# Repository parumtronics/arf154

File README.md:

# arf154 

Arf154 is an arduino compatible wireless network ready board.

The board core is the atsamr21g1x SoC. The device integrates a Cortex-M0 and a
IEEE 802.15.4 transceiver.

## Footprint

The design is targeting to be as compatible as possible with Arduino nano.

## How to program

The board can be programmed using the USB connector or trough the EMDBG using 
any Atmel software tools.

## Libraries

At this moment, there's no library but basic wireless communication libraries 
will be added in near future. Support for advanced features, as mesh network,
will be added later.

The board also is compatible with zigbee, 6lowpan and other network standart.

## Status

At this moment the schematics are almost done.

LICENSE: All work is released under the MIT license.

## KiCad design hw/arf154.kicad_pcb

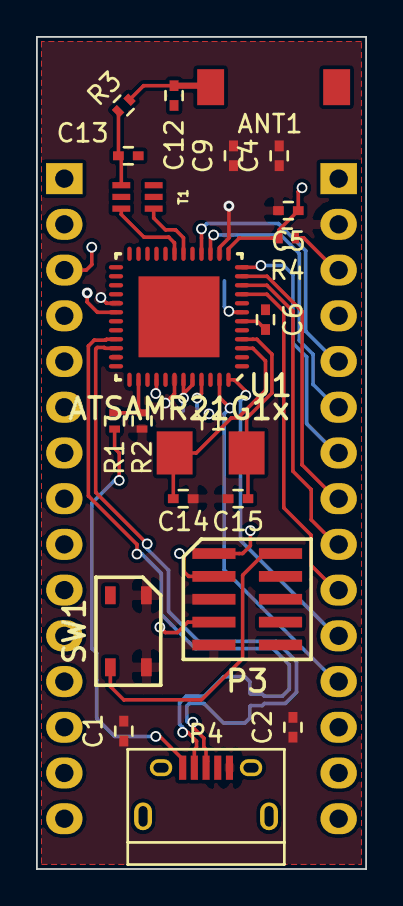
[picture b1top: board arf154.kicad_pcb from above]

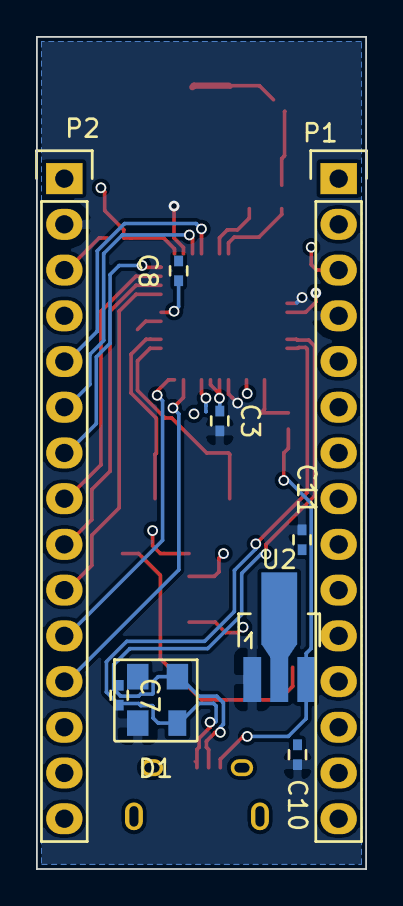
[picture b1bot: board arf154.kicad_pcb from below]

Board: 4 copper layers, 18.3 x 46.2 mm, 30 parts (9 on the bottom side), 27 nets.

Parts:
ANT1: antenna; CHIPANTENNA2dBi
C1: 10uF; C_0402
C2, C3, C4, C5, C6, C7, C8, C10: 100n; C_0402
C9, C11: 10u; C_0402
C12, C13: xF; C_0402
C14, C15: 18pF; C_0402
D1: PRTR5V0U2X; SOT143B
P1: Cn1; Pin_Header_Straight_1x15
P2: Cn2; Pin_Header_Straight_1x15
P3: CONN_02X05; CMxDBG
P4: USB_B; USB_Micro-B
R1, R2: 100K; R_0402
R3: xR; R_0402
R4: 10K; R_0402
SW1: SW_PUSH; tactileswitch
T1: 2450BM15A0015; JBALUN
U1: ATSAMR21G1x; QFN48EP
U2: AZ1117C; SOT89-3_Housing_Handsoldering
Y1: 16MHz; 2SMD

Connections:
/MainProcessor/BD+: T1.4, U1.18
/MainProcessor/BD-: T1.3, U1.19
/MainProcessor/PA4: P2.10, U1.9
/MainProcessor/PA5: P2.9, U1.10
/MainProcessor/PA6: P2.8, U1.11
/MainProcessor/PA7: P2.7, U1.12
/MainProcessor/PA8: P2.6, U1.15
/MainProcessor/PA9: P2.5, U1.16
/MainProcessor/PA22: U1.31, U1.37
/MainProcessor/PA23: R1.2, R2.1, U1.32, U1.38
/MainProcessor/PB2: P2.12, U1.47
/MainProcessor/PB3: P2.11, U1.48
/MainProcessor/RST: C7.1, P1.3, P2.3, P3.10, R4.1, SW1.2, U1.40
/MainProcessor/SWCLK: P3.4, U1.45
/MainProcessor/SWDIO: P3.2, U1.46
/Sheet557215E3/D+: D1.3, P4.2, U1.33
/Sheet557215E3/D-: D1.2, P4.3, U1.34
GND: C1.2, C2.2, C3.2, C4.2, C5.2, C7.2, C10.2, C11.2, C14.2, C15.2, D1.1, P1.4, P2.2, P3.3, P3.5, P3.9, P4.4, P4.5, R2.2, SW1.1, U1.14, U1.29, U1.35, U1.42, U2.1
GNDA: C6.2, C8.2, C9.2, U1.5, U1.8, U1.17, U1.20
GNDREF: C12.2, C13.2, T1.2, T1.5, T1.6
unnamed: ANT1.1, C12.1, R3.2
unnamed: C13.1, R3.1, T1.1
unnamed: C14.1, U1.3, Y1.1
unnamed: C15.1, U1.4, Y1.2
VAA: C6.1, C8.1, C9.1, U1.6, U1.7
VCC: C10.1, D1.4, P4.1, R1.1, U2.3
VDD: C1.1, C2.1, C3.1, C4.1, C5.1, C11.1, P2.14, P3.1, R4.2, U1.13, U1.30, U1.36, U1.43, U1.44, U2.2

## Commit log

2015-05-17 Add processing library
2015-05-17 Cleanning .bak files
2015-06-04 Initial
2015-06-04 Adding atsamr21q1x
2015-06-04 Fix directory structure
2015-06-04 Minor fix in MainProcessor circuit
2015-06-04 Adding top design and .gitignore
2015-06-05 Added Balun and edbg connector
2015-06-05 Schematics for main processor done
2015-06-05 Added linear voltage regulator 3V3
2015-06-05 Fix naming of atsamr21G SOC
2015-06-06 Added USB circuit
2015-06-10 Adding README
2015-06-14 USB connections made, need to add protection in VBUS power flag connection to avoid problems when not powered from USB
2015-06-16 First schematics done. Need to finish connections and add power separation of VBUS-VCC
2015-06-16 Adding the cmp file with assigned parts footprint
2015-06-17 README update, Schematics almost done(need to finish power section)
2015-06-26 Started layout, minor gitignore modification
2015-06-26 Fix libraries ignored
2015-06-28 Schematics change for a smaller regulator, added a new sch module, layout update
2015-06-28 Added Balun, modules library needs better naming
2015-06-28 added auto generated rescue lib
2015-06-28 Modified power regulator
2015-06-28 Layout update, footprint changed to 0402, atsam component fix
2015-07-02 Layout for the analog pads and DRC fix on the USB signals
2015-07-04 Layout updated, need improvement on ground layers and a power switch
2015-07-07 Layout modifications
